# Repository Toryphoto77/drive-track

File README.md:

# 驰迹 DriveTrack

> 把每一次驾驶，记录成能被复盘的数据。

驰迹是一款为「认真开车的人」做的驾驶记录 App：汽车、摩托、卡丁车三种模式，一键开始记录。轨迹、车速、G 值、姿态、定位精度全程留存，赛道日还能自动计时、逐圈复盘。

黑色 HUD 界面，没有导航式的杂乱信息：开的时候只看该看的，停下来再慢慢看数据。

## 我们想做的事

市面上的行车记录大多停在「画一条线」这一步：轨迹有了，但看不出哪一脚刹车早了、哪一个弯出得慢了。驰迹想把它往前推一步——同一份数据，既能在赛道上告诉你这一圈差在哪，也能在日常通勤后告诉你这段路开得稳不稳。

三条原则贯穿整个产品：

- **记录不该打扰驾驶**：记录界面只有必要的数字，语音播报代替盯屏，倒计时带强震反馈。
- **数据留在你手里**：默认只存本机，云端上传、公开行程都是手动操作，不做自动同步。
- **结论要看得懂**：不给一串看不懂的曲线，给圈速、Delta、分段着色和一句能执行的提示。

## 核心功能

### 三种模式

- **汽车 / 摩托**：街道记录，超速与 GPS 丢失语音提醒，出行天气播报。
- **卡丁车**：为赛道日准备的精简计时界面——大号圈速、圈号、左右两道 Delta 色条，扫一眼就知道快慢。
- 历史里的骑行行程仍可正常打开与查看。

### 赛道计时

- 进入赛道或卡丁前会校验外接定位是否就绪（是否连接、是否只输出二进制、是否已有定位、采样率是否达到 5Hz），不满足时直接说明原因并跳到设备页，避免记出一堆无效数据。
- 过线瞬间三重反馈：语音播报圈速、短震动、全屏闪一帧（绿色代表个人最佳，红色代表慢于参照）。
- 大字当前圈 + 分段着色 + 官方分段点 + 带符号 Delta，默认以本场最佳圈为参照。
- 赛道库收录 F1、中国系列与经典赛道共 78 条，几何逐条核对，长度对照 FIA 官方数据。
- 0–100 / 100–0 性能测试；驾驶习惯评分，扣分项逐条透明可见。

### 赛后复盘

- 数据页为车队遥测风格：速度、海拔、弯道曲线共用一条时间轴联动。
- 完赛汇总：圈速折线配逐圈数据（最佳圈高亮），给出中位圈、平均圈、圈速标准差与一致性，一眼看出这场的节奏是稳还是崩。
- 曲线 + 着色线路，不依赖视频也能复盘。
- 行程可导出、可分享；赛道包支持官方更新与本地编辑，官方更新不会覆盖你的改动。

### 外接设备

- 单入口扫描外接定位：DEXIAN D1、RaceBox、Dragy、Qstarz 等，通用 NMEA 兼容（私有协议以实测为准）。
- 自研 GPS + IMU 硬件方案推进中（ESP32-S3 + NEO-M9N + BMI088 + 气压计，车顶安装）。

### 云端（可选）

- 不登录也能用完整体验；登录后行程只在你点上传时才上传。
- 行程与公开资料可设为公开，默认仅本人可见。

## 下载

最新版见 [Releases](https://github.com/Toryphoto77/drive-track/releases/latest)（当前 v1.7.4）。按手机架构选一个，大多数手机用 arm64-v8a：

| 安装包 | 适用机型 |
| --- | --- |
| `DriveTrack-v*-release-arm64-v8a.apk` | 绝大多数安卓手机 |
| `DriveTrack-v*-release-armeabi-v7a.apk` | 老款 32 位手机 |
| `DriveTrack-v*-release-x86_64.apk` | x86 平板 / 模拟器 |

直接覆盖安装即可升级，不要卸载重装（本机行程存在本地，卸载会丢）。

App 内「关于 → 检查更新」会自动匹配当前架构的安装包，并对下载文件做 SHA-256 校验。

## 已知限制

- 传感器零偏校准只存内存，重启 App 需重新校零。
- 外接定位协议以通用 NMEA 为主，私有协议设备以实测为准。
- 路网来自公开 Overpass 服务，服务繁忙或网络不通时会提示失败原因，可手动重拉，上次成功的数据按位置缓存。
- 个人页填写的邮箱只存本机，不用于登录。

## 反馈

问题、建议、赛道数据纠错都欢迎提 [Issue](https://github.com/Toryphoto77/drive-track/issues)。

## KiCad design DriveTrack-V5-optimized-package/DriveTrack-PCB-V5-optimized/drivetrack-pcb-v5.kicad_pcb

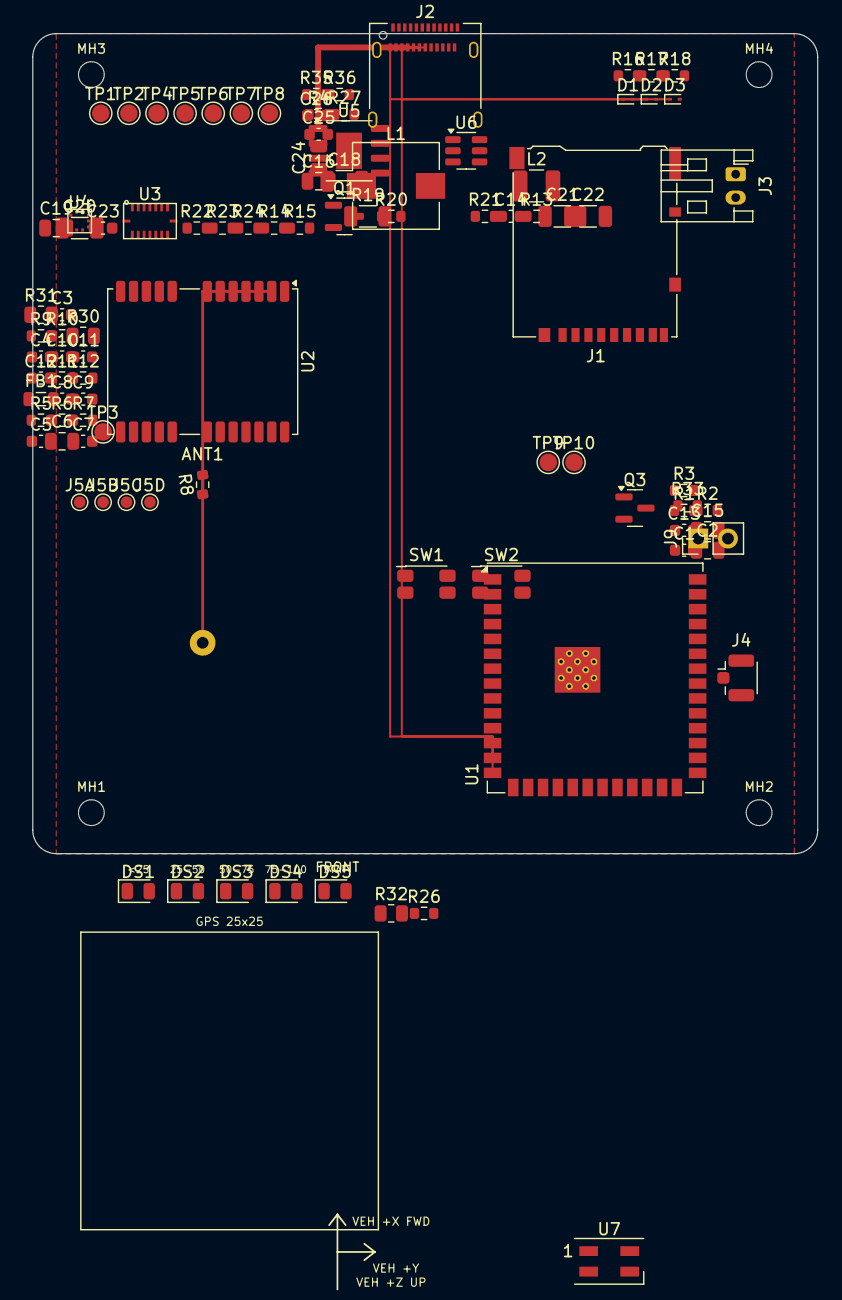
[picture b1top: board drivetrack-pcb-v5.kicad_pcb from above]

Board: 4 copper layers, 67.0 x 70.0 mm, 103 parts (0 on the bottom side), 63 nets.

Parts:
ANT1: GPS_Patch_25x25
C1, C4, C5, C7, C8, C9, C11, C12, C13, C14, C23, C25, C26: 100n; C_0603_1608Metric
C2, C6, C15, C16, C19, C24: 10u; C_0805_2012Metric
C3, C10: 1u; C_0603_1608Metric
C18, C20, C21, C22: 22u; C_1206_3216Metric
D1: ESD9B5.0ST5G; D_SOD-923
D2, D3: ESD9B3.3ST5G; D_SOD-923
DS1, DS2, DS3, DS4, DS5: LED 0805; LED_0805_2012Metric
FB1: FB 120R@100MHz; L_0805_2012Metric
J1: microSD push-push; microSD_HC_Hirose_DM3AT-SF-PEJM5
J2: USB-C 16P; USB_C_Receptacle_Amphenol_12401610E4-2A
J3: JST-PH 2.0mm; JST_PH_S2B-PH-K_1x02_P2.00mm_Horizontal
J4: U.FL (DNI); U.FL_Hirose_U.FL-R-SMT-1_Vertical
J5A: UART0_TX; TestPoint_Pad_D1.0mm
J5B: UART0_RX; TestPoint_Pad_D1.0mm
J5C: +3V3; TestPoint_Pad_D1.0mm
J5D: GND; TestPoint_Pad_D1.0mm
J9: solder pads DNI; PinHeader_1x02_P2.54mm_Vertical
L1: 1u; L_7.3x7.3_H4.5
L2: 2.2u; L_1210_3225Metric
MH1, MH2, MH3, MH4: MH 2.2mm NPTH; MountingHole_2.2mm
Q1, Q3: 2N7002; SOT-23
R1, R2, R5, R6, R9, R10, R13, R14, R15, R23: 10k; R_0603_1608Metric
R3: 330; R_0603_1608Metric
R4: 0.5R; R_0603_1608Metric
R7, R8, R18: 0R; R_0603_1608Metric
R11, R12: 4.7k; R_0603_1608Metric
R16, R17: 5.1k; R_0603_1608Metric
R19: 100R; R_1206_3216Metric
R20, R33: 1k; R_0603_1608Metric
R21, R24, R35, R36: 100k; R_0603_1608Metric
R22: 33k; R_0603_1608Metric
R26: 330R; R_0603_1608Metric
R27: 2R; R_0603_1608Metric
R30, R31: 100k; R_0805_2012Metric
R32: 330; R_0805_2012Metric
SW1: BOOT; SW_SPST_EVQP7A
SW2: RST; SW_SPST_EVQP7A
TP1: TP +3V3; TestPoint_Pad_D1.5mm
TP2: TP GND; TestPoint_Pad_D1.5mm
TP3: TP GPS_PPS; TestPoint_Pad_D1.5mm
TP4: TP BAT; TestPoint_Pad_D1.5mm
TP5: TP VBAT_DIV; TestPoint_Pad_D1.5mm
TP6: TP UART0_TX; TestPoint_Pad_D1.5mm
TP7: TP UART0_RX; TestPoint_Pad_D1.5mm
TP8: TP IO2; TestPoint_Pad_D1.5mm
TP9: TP KEY; TestPoint_Pad_D1.5mm
TP10: TP KEY_GND; TestPoint_Pad_D1.5mm
U1: ESP32-S3-WROOM-1U-N16R8; ESP32-S3-WROOM-1U
U2: NEO-M9N; ublox_NEO
U3: BMI088; BMI088_LGA-16_3.0x4.5mm
U4: BMP390; BMP390_LGA-10_2.0x2.0mm
U5: IP5306; IP5306_eSOP-8_3.9x4.9mm_EP2.21x3.10
U6: TPS563201; SOT-23-6
U7: SK6812MINI; LED_SK6812MINI_PLCC4_3.5x3.5mm_P1.75mm

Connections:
+3V3: C1.2, C2.2, C4.2, C9.2, C10.2, C11.2, C12.2, C13.2, C14.2, C15.2, C21.2, C22.2, FB1.2, J1.4, J5C.1, L2.2, R1.2, R2.2, R9.2, R10.2, R11.2, R12.2, R13.2, R14.2, R15.2, R22.1, TP1.1, U1.2, U3.3, U3.11, U4.1, U4.5, U4.6, U4.10, U7.4
+5V: C19.2, C20.1, C25.1, R19.1, R24.1, U5.8, U6.3
BARO_SCL: R12.1, U1.17, U4.2
BARO_SDA: R11.1, U1.12, U4.4
BAT: C18.2, J3.1, J9.1, L1.2, R4.1, R30.1, TP4.1
BOOT: R1.1, SW1.1, U1.27
DUMMY_EN: R20.2, U1.23
EN: C3.2, R2.1, SW2.1, U1.3
GND: C1.1, C2.1, C3.1, C4.1, C5.1, C6.1, C7.1, C8.1, C9.1, C10.1, C11.1, C12.1, C13.1, C14.1, C15.1, C16.1, C18.1, C19.1, C20.2, C21.1, C22.1, C24.1, C25.2, C26.2, D1.2, D2.2, D3.2, DS1.1, DS2.1, DS3.1, DS4.1, DS5.1, J1.6, J1.9, J1.11, J2.A1, J2.A12, J2.B1, J2.B12, J3.2, J4.2, J5D.1, J9.2, Q1.2, Q3.2, R16.1, R17.1, R18.2, R21.1, R23.1, R31.2, R36.2, SW1.2, SW2.2, TP2.1, TP10.1, U1.1, U1.40, U1.41, U2.7, U2.10, U2.12, U2.13, U2.24, U3.2, U3.4, U3.6, U3.7, U4.3, U4.8, U4.9, U5.9, U6.1, U7.2
GPS_PPS: TP3.1, U1.4, U2.3
GPS_RF: R8.2, U2.11
GPS_RX: U1.11, U2.20
GPS_TX: U1.10, U2.21
GPS_VCC: C5.2, C6.2, C7.2, FB1.1, R5.2, R6.2, R7.1, R7.2, U2.22, U2.23
IMU_CS1: R9.1, U1.18, U3.14
IMU_CS2: R10.1, U1.19, U3.5
IMU_INT1: U1.5, U3.16
IMU_INT3: U1.6, U3.12
IMU_MISO: U1.9, U3.10, U3.15
IMU_MOSI: U1.8, U3.9
IMU_SCK: U1.22, U3.8
IO2: R32.2, TP8.1, U1.38
KEY: Q3.3, TP9.1, U5.5
KEY_CTRL: R33.1, U1.34
KEY_GATE: Q3.1, R33.2
LED1: DS1.2, U5.2
LED2: DS2.2, U5.3
LED3: DS3.2, U5.4
LED4: DS4.2, R32.1
M9N_RESET: R6.1, U2.8
M9N_SAFEBOOT: R5.1, U2.1
unnamed: ANT1.1, R8.1
unnamed: C24.2, R27.1
unnamed: J2.S1, R18.1
unnamed: Q1.3, R19.2
unnamed: Q1.1, R20.1, R21.2
unnamed: C8.2, U2.9
unnamed: R4.2, U5.6
unnamed: L1.1, U5.7
unnamed: R24.2, U6.5
unnamed: C23.2, L2.1, U6.2
unnamed: C23.1, U6.6
unnamed: R22.2, R23.2, U6.4
unnamed: R3.1, U7.3
RGB_DIN: R3.2, U1.25
SD_CD: J1.10, R15.1, U1.21
SD_CS: J1.2, U1.20
SD_DAT1: J1.8, R13.1
SD_DAT2: J1.1, R14.1
SD_MISO: J1.7, U1.33
SD_MOSI: J1.3, U1.32
SD_SCK: J1.5, U1.31
STAT_ANODE: DS5.2, R26.1
STAT_LED: R26.2, U1.7
UART0_RX: J5B.1, TP7.1, U1.36
UART0_TX: J5A.1, TP6.1, U1.37
USB_CC1: J2.A5, R16.2
USB_CC2: J2.B5, R17.2
USB_DM: D3.1, J2.A7, J2.B7, U1.13
USB_DP: D2.1, J2.A6, J2.B6, U1.14
VBAT_DIV: R30.2, R31.1, TP5.1, U1.39
VBUS: C16.2, D1.1, J2.A4, J2.A9, J2.B4, J2.B9, R27.2, R35.1, U5.1
VBUS_DET: C26.1, R35.2, R36.1, U1.35

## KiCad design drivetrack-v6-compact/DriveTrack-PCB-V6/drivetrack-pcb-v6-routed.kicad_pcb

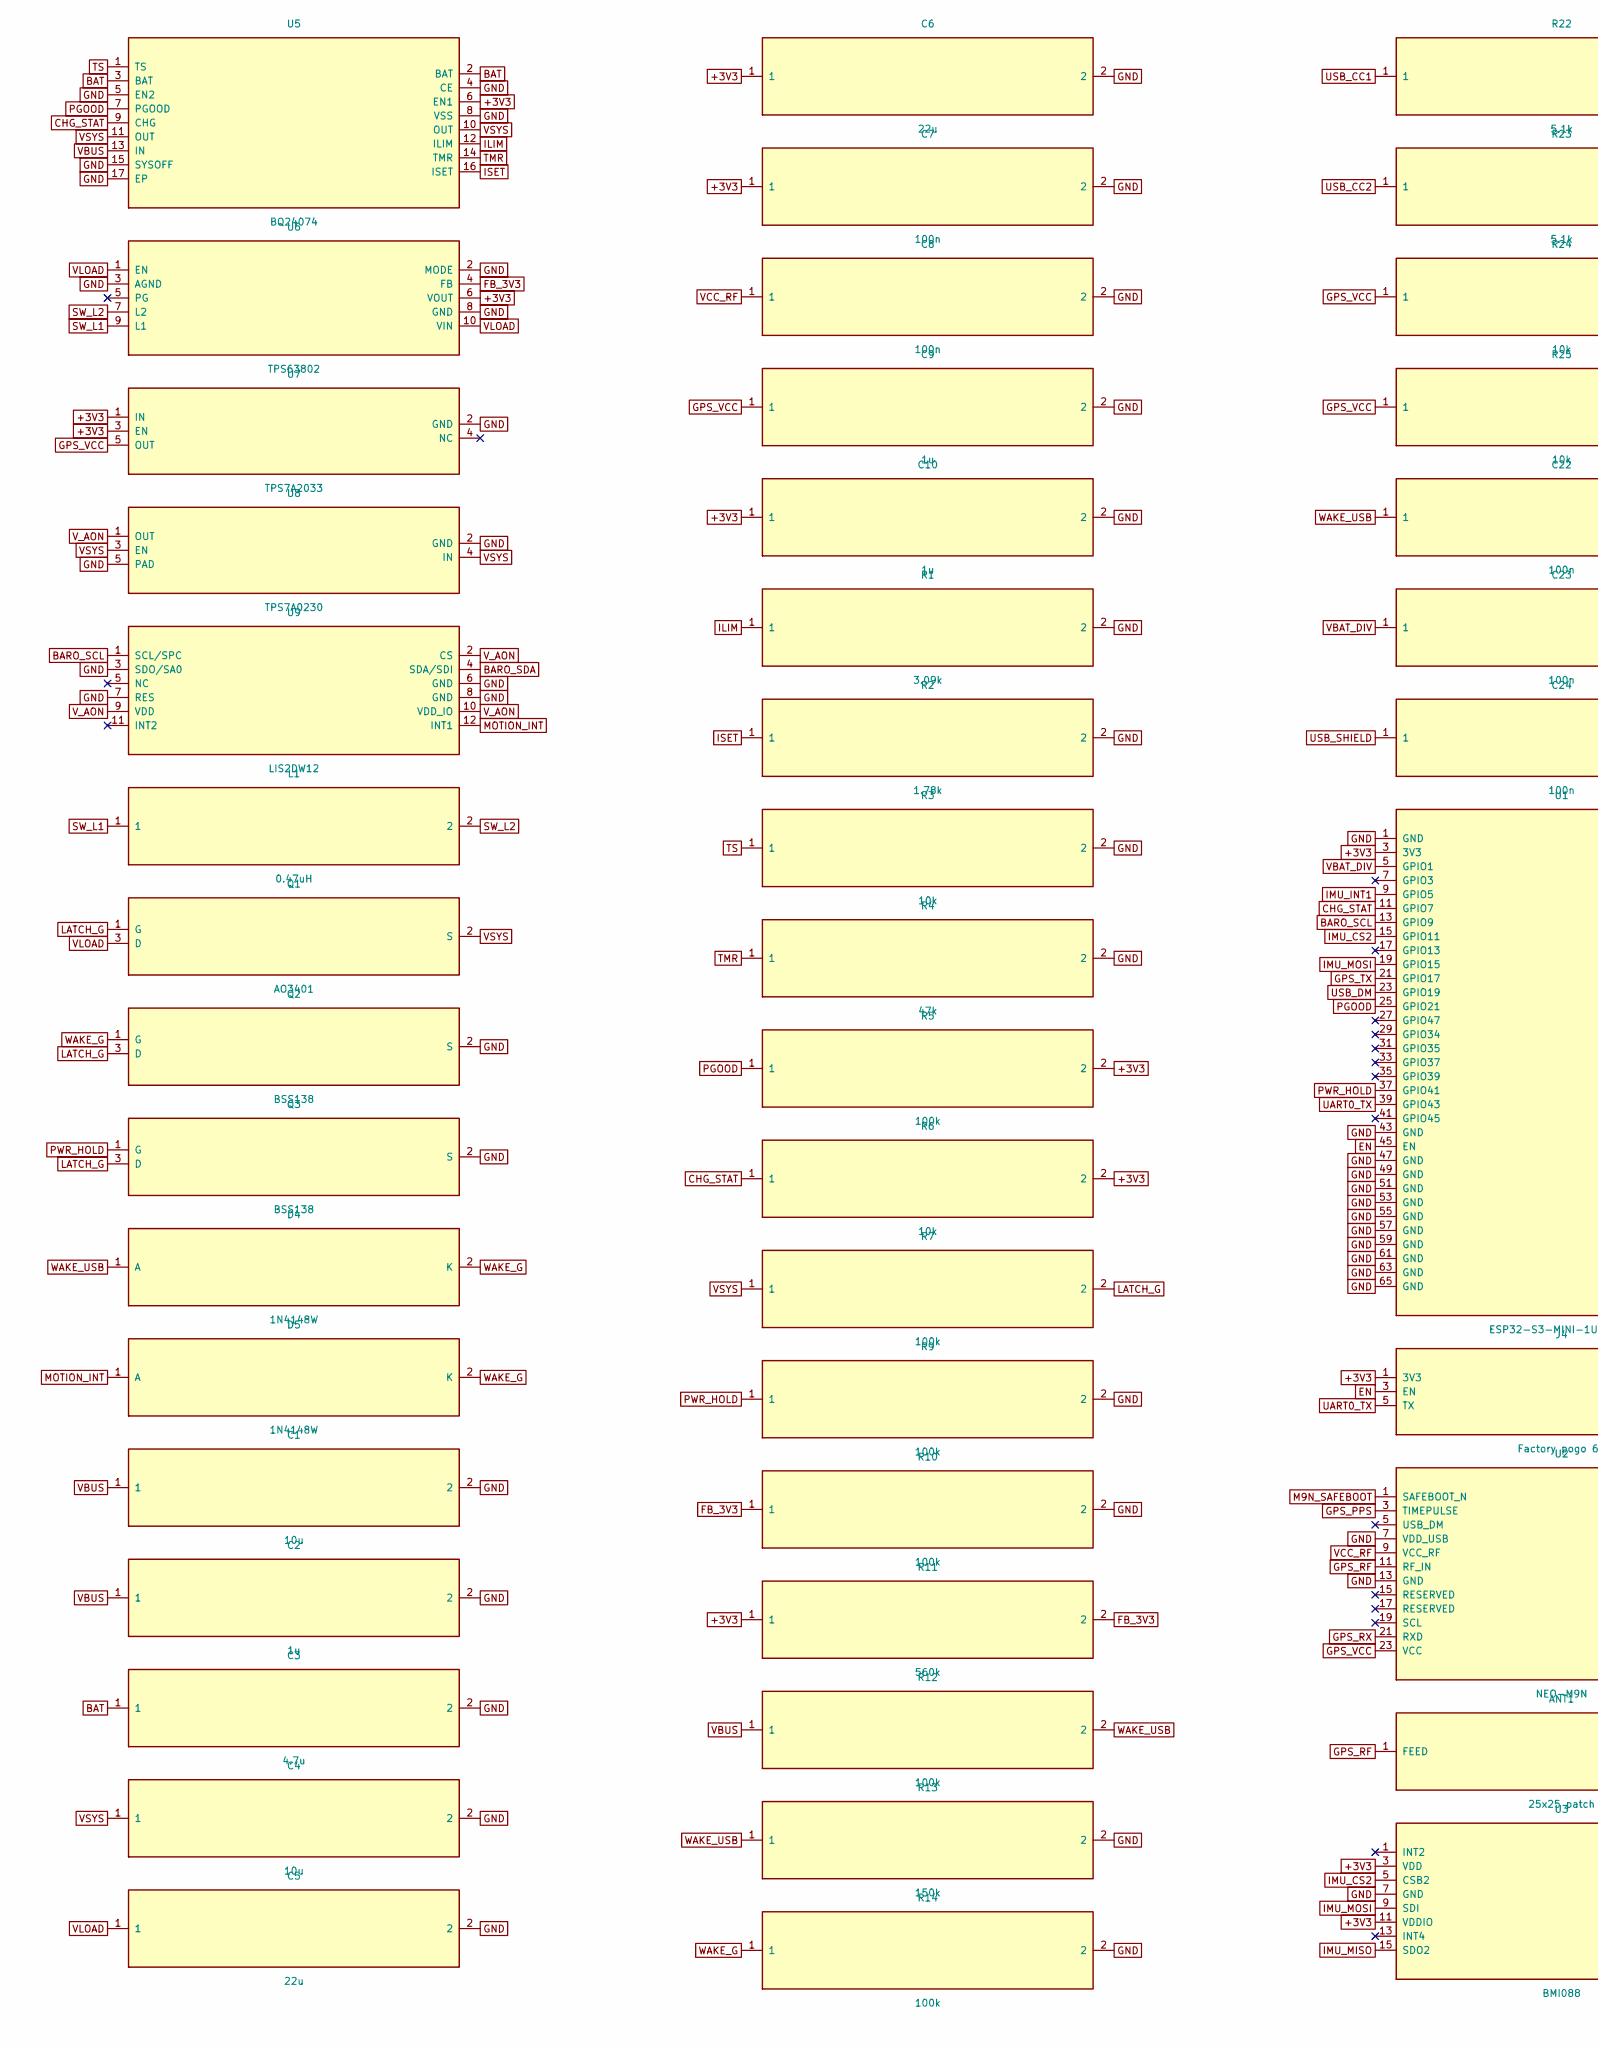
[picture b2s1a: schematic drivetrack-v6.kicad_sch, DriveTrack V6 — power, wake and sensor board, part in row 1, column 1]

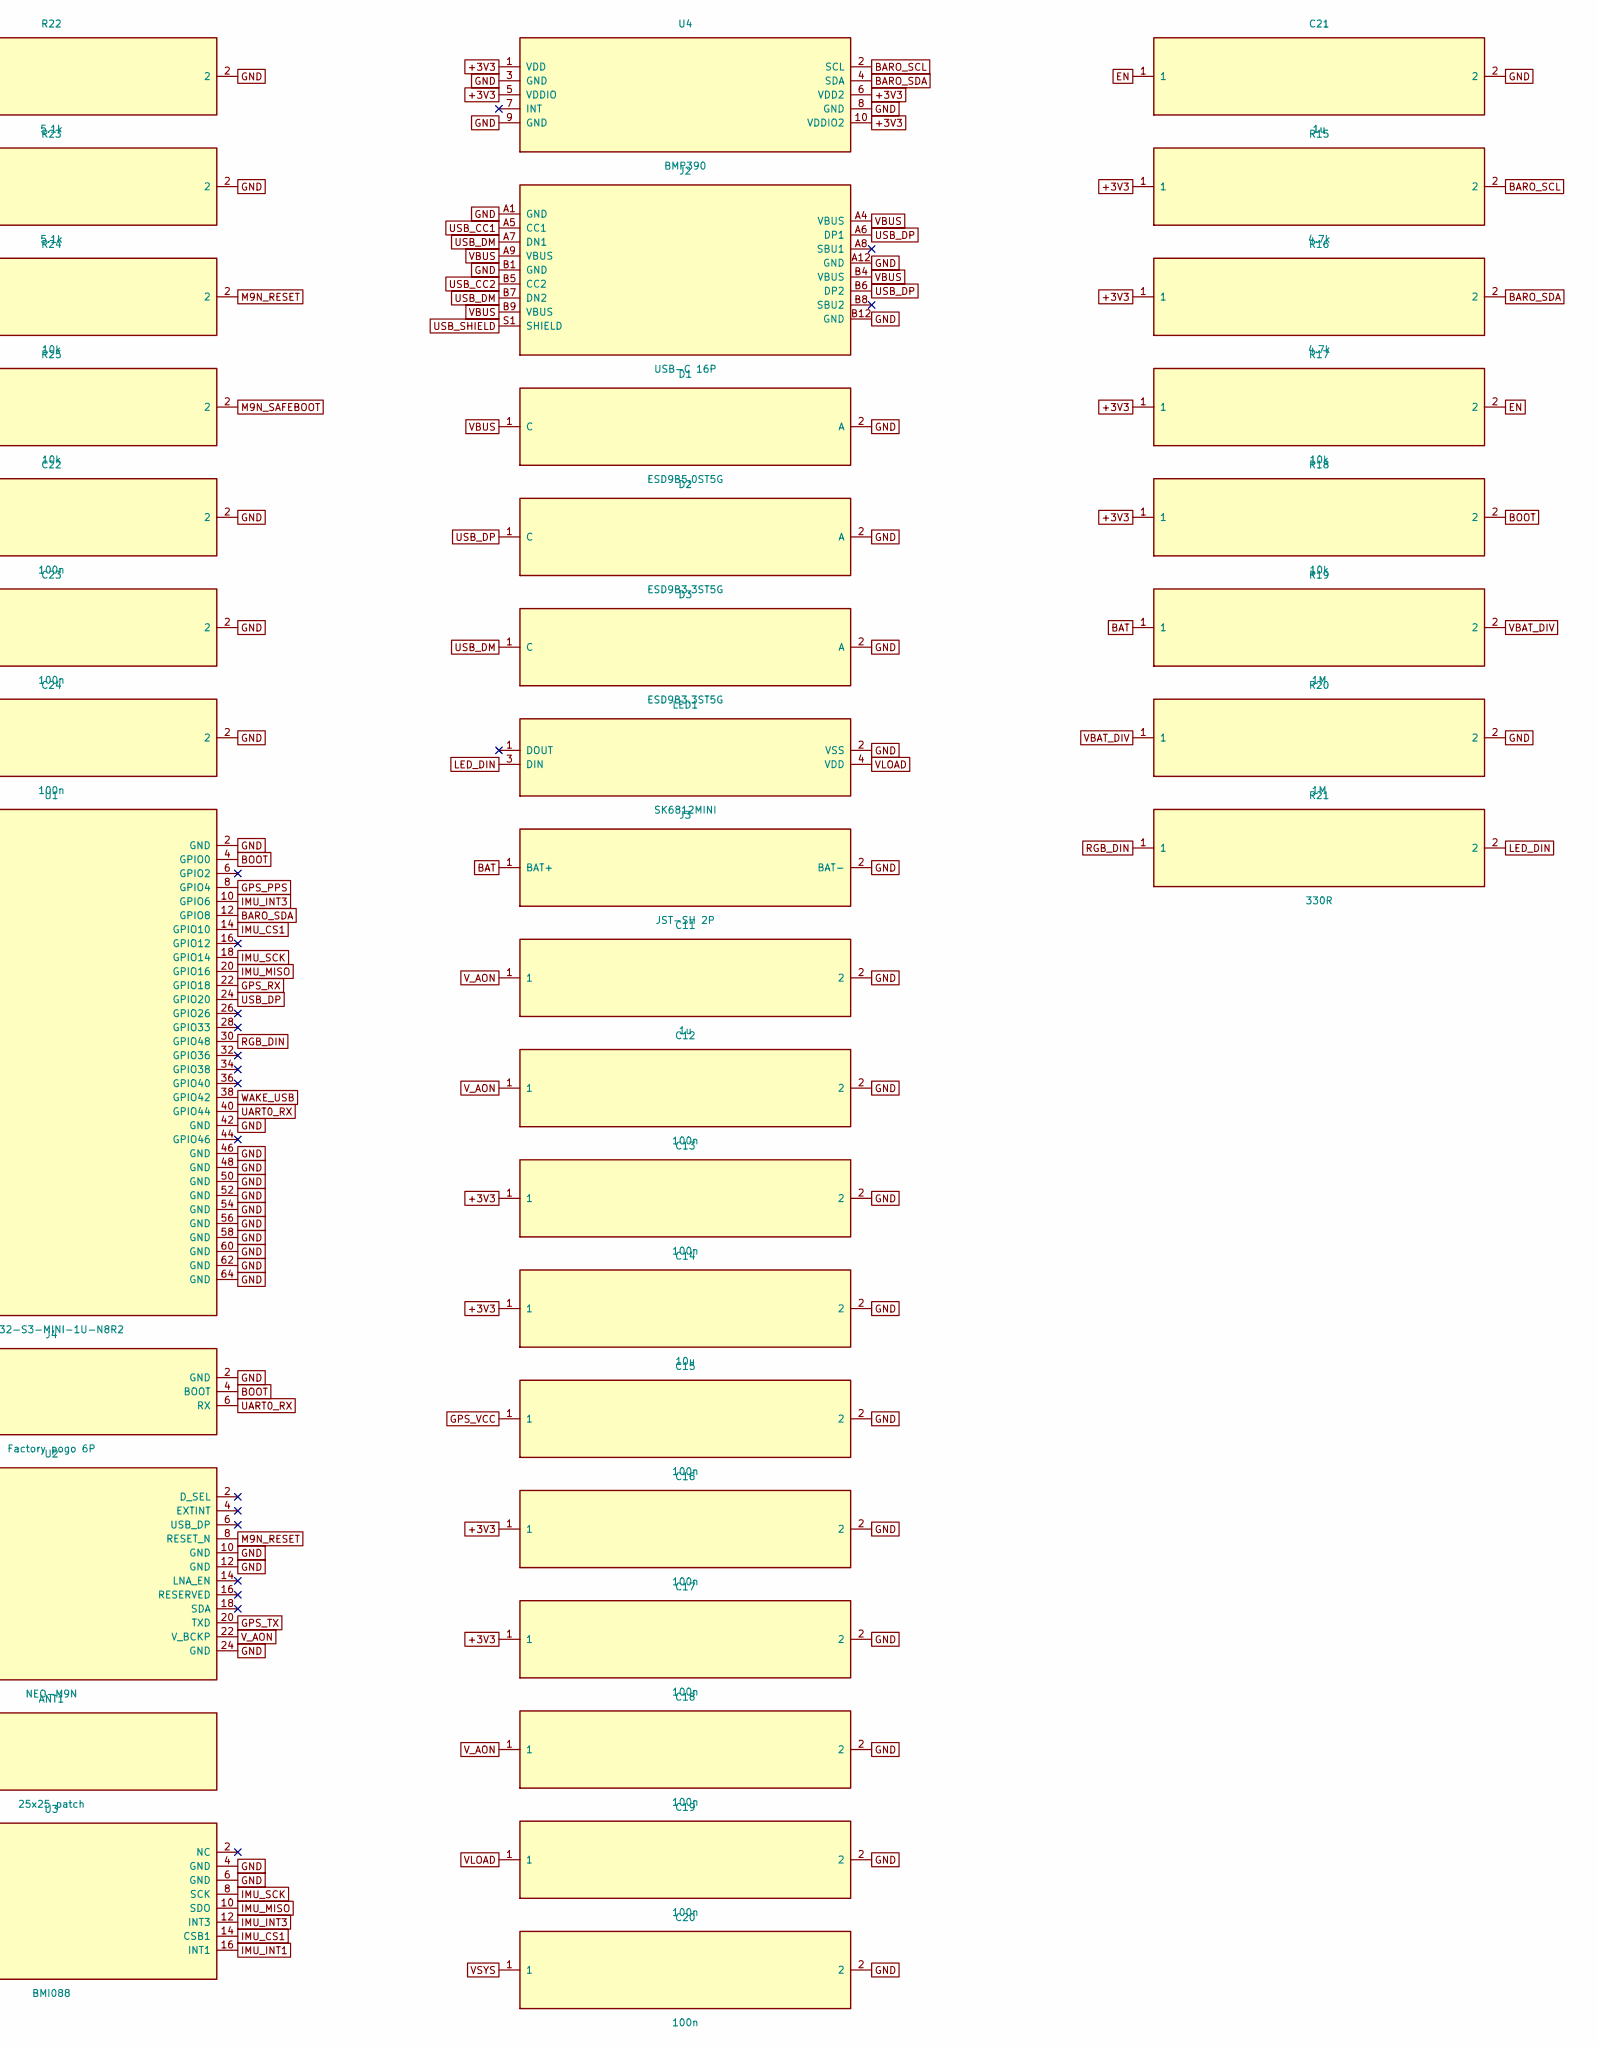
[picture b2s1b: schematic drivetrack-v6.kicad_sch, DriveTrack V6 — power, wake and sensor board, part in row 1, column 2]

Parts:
ANT1: 25x25 patch; GPS_Patch_25x25
C1, C4, C14: 10u; C_0805_2012Metric
C2, C9, C10, C11, C21: 1u; C_0603_1608Metric
C3: 4.7u; C_0805_2012Metric
C5, C6: 22u; C_0805_2012Metric
C7, C8, C12, C13, C15, C16, C17, C18, C19, C20, C22, C23, C24: 100n; C_0402_1005Metric
D1: ESD9B5.0ST5G; D_SOD-923
D2, D3: ESD9B3.3ST5G; D_SOD-923
D4, D5: 1N4148W; D_SOD-323
J2: USB-C 16P; USB_C_Receptacle_Amphenol_12401610E4-2A
J3: JST-SH 2P; JST_SH_SM02B-SRSS-TB_1x02-1MP_P1.00mm_Horizontal
J4: Factory pogo 6P; Pogo_6_1.5mm
L1: 0.47uH; L_4x4_H2
LED1: SK6812MINI; LED_SK6812MINI_PLCC4_3.5x3.5mm_P1.75mm
Q1: AO3401; SOT-23
Q2, Q3: BSS138; SOT-23
R1: 3.09k; R_0402_1005Metric
R2: 1.78k; R_0402_1005Metric
R3, R6, R17, R18, R24, R25: 10k; R_0402_1005Metric
R4: 47k; R_0402_1005Metric
R5, R7, R9, R10, R12, R14: 100k; R_0402_1005Metric
R11: 560k; R_0402_1005Metric
R13: 150k; R_0402_1005Metric
R15, R16: 4.7k; R_0402_1005Metric
R19, R20: 1M; R_0402_1005Metric
R21: 330R; R_0402_1005Metric
R22, R23: 5.1k; R_0402_1005Metric
U1: ESP32-S3-MINI-1U-N8R2; ESP32-S3-MINI-1
U2: NEO-M9N; ublox_NEO
U3: BMI088; BMI088_LGA-16_3.0x4.5mm
U4: BMP390; BMP390_LGA-10_2.0x2.0mm
U5: BQ24074; VQFN-16-1EP_3x3mm_P0.5mm_EP1.6x1.6mm
U6: TPS63802; VSON-10-3x2mm_P0.5mm_TPS63802
U7: TPS7A2033; SOT-23-5
U8: TPS7A0230; Texas_X2SON-4_1x1mm_P0.65mm
U9: LIS2DW12; LGA-12_2x2mm_P0.5mm

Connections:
+3V3: C6.1, C7.1, C10.1, C13.1, C14.1, C16.1, C17.1, J4.1 (3V3), R5.2, R6.2, R11.1, R15.1, R16.1, R17.1, R18.1, U1.3 (3V3), U3.3 (VDD), U3.11 (VDDIO), U4.1 (VDD), U4.5 (VDDIO), U4.6 (VDD2), U4.10 (VDDIO2), U5.6 (EN1), U6.6 (VOUT), U7.1 (IN), U7.3 (EN)
BARO_SCL: R15.2, U1.13 (GPIO9), U4.2 (SCL), U9.1 (SCL/SPC)
BARO_SDA: R16.2, U1.12 (GPIO8), U4.4 (SDA), U9.4 (SDA/SDI)
BAT: C3.1, J3.1 (BAT+), R19.1, U5.2 (BAT), U5.3 (BAT)
BOOT: J4.4 (BOOT), R18.2, U1.4 (GPIO0)
CHG_STAT: R6.1, U1.11 (GPIO7), U5.9 (CHG)
EN: C21.1, J4.3 (EN), R17.2, U1.45 (EN)
FB_3V3: R10.1, R11.2, U6.4 (FB)
GND: C1.2, C2.2, C3.2, C4.2, C5.2, C6.2, C7.2, C8.2, C9.2, C10.2, C11.2, C12.2, C13.2, C14.2, C15.2, C16.2, C17.2, C18.2, C19.2, C20.2, C21.2, C22.2, C23.2, C24.2, D1.2 (A), D2.2 (A), D3.2 (A), J2.A1 (GND), J2.A12 (GND), J2.B1 (GND), J2.B12 (GND), J3.2 (BAT-), J4.2 (GND), LED1.2 (VSS), Q2.2 (S), Q3.2 (S), R1.2, R2.2, R3.2, R4.2, R9.2, R10.2, R13.2, R14.2, R20.2, R22.2, R23.2, U1.1 (GND), U1.2 (GND), U1.42 (GND), U1.43 (GND), U1.46 (GND), U1.47 (GND), U1.48 (GND), U1.49 (GND), U1.50 (GND), U1.51 (GND), U1.52 (GND), U1.53 (GND), U1.54 (GND), U1.55 (GND), U1.56 (GND), U1.57 (GND), U1.58 (GND), U1.59 (GND), U1.60 (GND), U1.61 (GND), U1.62 (GND), U1.63 (GND), U1.64 (GND), U1.65 (GND), U2.7 (VDD_USB), U2.10 (GND), U2.12 (GND), U2.13 (GND), U2.24 (GND), U3.4 (GND), U3.6 (GND), U3.7 (GND), U4.3 (GND), U4.8 (GND), U4.9 (GND), U5.4 (CE), U5.5 (EN2), U5.8 (VSS), U5.15 (SYSOFF), U5.17 (EP), U6.2 (MODE), U6.3 (AGND), U6.8 (GND), U7.2 (GND), U8.2 (GND), U8.5 (PAD), U9.3 (SDO/SA0), U9.6 (GND), U9.7 (RES), U9.8 (GND)
GPS_PPS: U1.8 (GPIO4), U2.3 (TIMEPULSE)
GPS_RF: ANT1.1, U2.11 (RF_IN)
GPS_RX: U1.22 (GPIO18), U2.21 (RXD)
GPS_TX: U1.21 (GPIO17), U2.20 (TXD)
GPS_VCC: C9.1, C15.1, R24.1, R25.1, U2.23 (VCC), U7.5 (OUT)
ILIM: R1.1, U5.12 (ILIM)
IMU_CS1: U1.14 (GPIO10), U3.14 (CSB1)
IMU_CS2: U1.15 (GPIO11), U3.5 (CSB2)
IMU_INT1: U1.9 (GPIO5), U3.16 (INT1)
IMU_INT3: U1.10 (GPIO6), U3.12 (INT3)
IMU_MISO: U1.20 (GPIO16), U3.10 (SDO), U3.15 (SDO2)
IMU_MOSI: U1.19 (GPIO15), U3.9 (SDI)
IMU_SCK: U1.18 (GPIO14), U3.8 (SCK)
ISET: R2.1, U5.16 (ISET)
LATCH_G: Q1.1 (G), Q2.3 (D), Q3.3 (D), R7.2
LED_DIN: LED1.3 (DIN), R21.2
M9N_RESET: R24.2, U2.8 (RESET_N)
M9N_SAFEBOOT: R25.2, U2.1 (SAFEBOOT_N)
MOTION_INT: D5.1 (A), U9.12 (INT1)
PGOOD: R5.1, U1.25 (GPIO21), U5.7 (PGOOD)
PWR_HOLD: Q3.1 (G), R9.1, U1.37 (GPIO41)
RGB_DIN: R21.1, U1.30 (GPIO48)
SW_L1: L1.1, U6.9 (L1)
SW_L2: L1.2, U6.7 (L2)
TMR: R4.1, U5.14 (TMR)
TS: R3.1, U5.1 (TS)
UART0_RX: J4.6 (RX), U1.40 (GPIO44)
UART0_TX: J4.5 (TX), U1.39 (GPIO43)
USB_CC1: J2.A5 (CC1), R22.1
USB_CC2: J2.B5 (CC2), R23.1
USB_DM: D3.1 (C), J2.A7 (DN1), J2.B7 (DN2), U1.23 (GPIO19)
USB_DP: D2.1 (C), J2.A6 (DP1), J2.B6 (DP2), U1.24 (GPIO20)
USB_SHIELD: C24.1, J2.S1 (SHIELD)
VBAT_DIV: C23.1, R19.2, R20.1, U1.5 (GPIO1)
VBUS: C1.1, C2.1, D1.1 (C), J2.A4 (VBUS), J2.A9 (VBUS), J2.B4 (VBUS), J2.B9 (VBUS), R12.1, U5.13 (IN)
VCC_RF: C8.1, U2.9 (VCC_RF)
VLOAD: C5.1, C19.1, LED1.4 (VDD), Q1.3 (D), U6.1 (EN), U6.10 (VIN)
VSYS: C4.1, C20.1, Q1.2 (S), R7.1, U5.10 (OUT), U5.11 (OUT), U8.3 (EN), U8.4 (IN)
V_AON: C11.1, C12.1, C18.1, U2.22 (V_BCKP), U8.1 (OUT), U9.2 (CS), U9.9 (VDD), U9.10 (VDD_IO)
WAKE_G: D4.2 (K), D5.2 (K), Q2.1 (G), R14.1
WAKE_USB: C22.1, D4.1 (A), R12.2, R13.1, U1.38 (GPIO42)

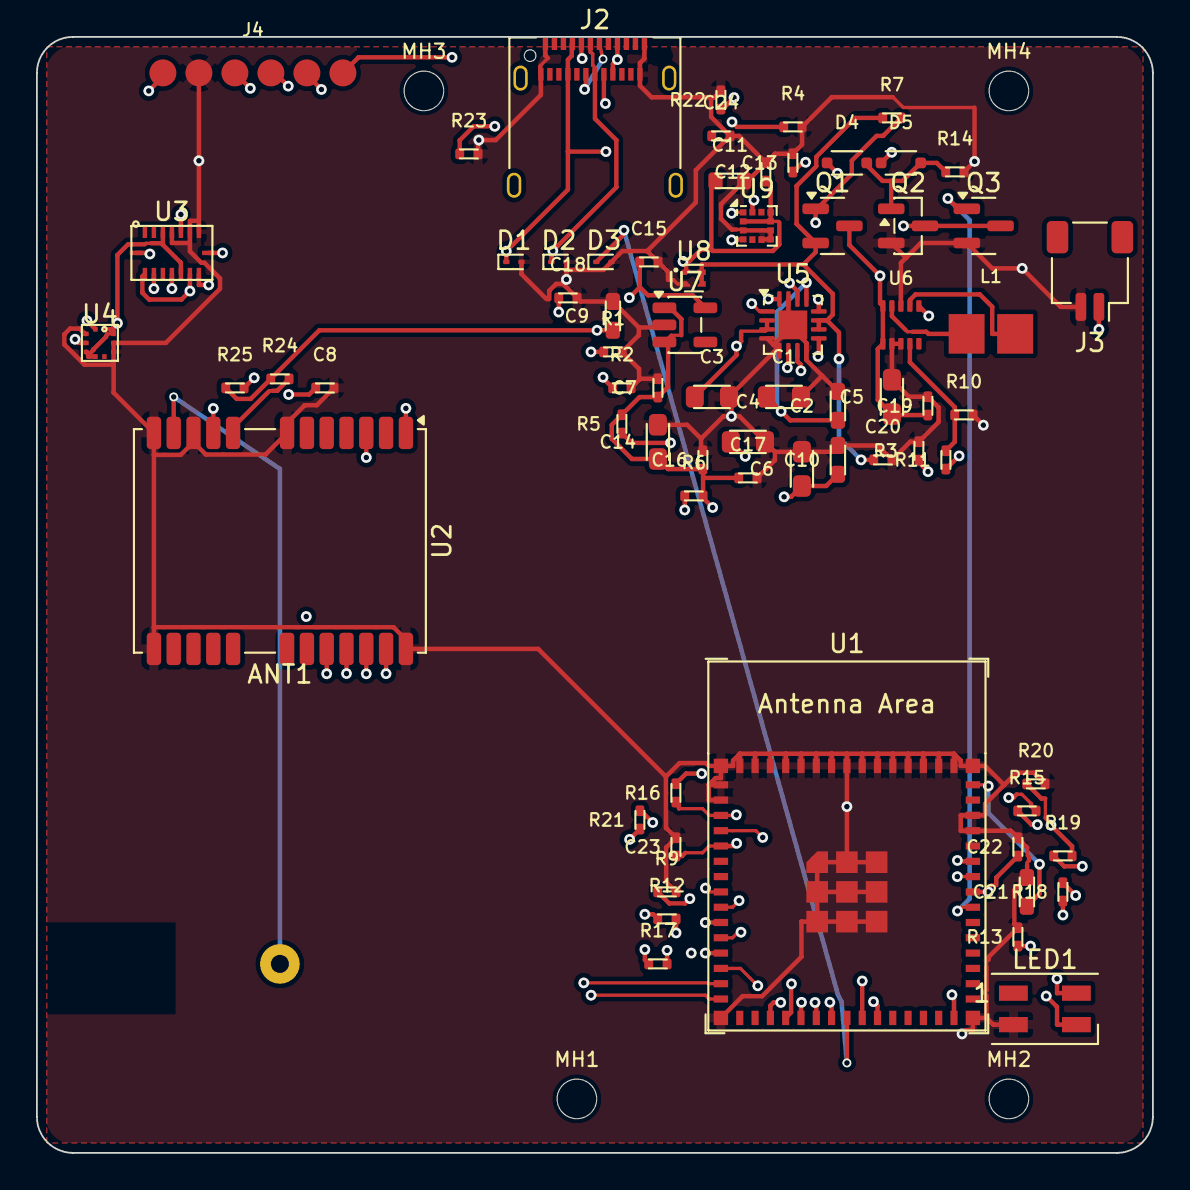
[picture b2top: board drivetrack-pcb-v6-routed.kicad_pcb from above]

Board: 4 copper layers, 62.0 x 62.0 mm, 75 parts (0 on the bottom side), 49 nets.

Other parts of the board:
MH1, MH2, MH3, MH4: M2 NPTH; MountingHole_2.2mm

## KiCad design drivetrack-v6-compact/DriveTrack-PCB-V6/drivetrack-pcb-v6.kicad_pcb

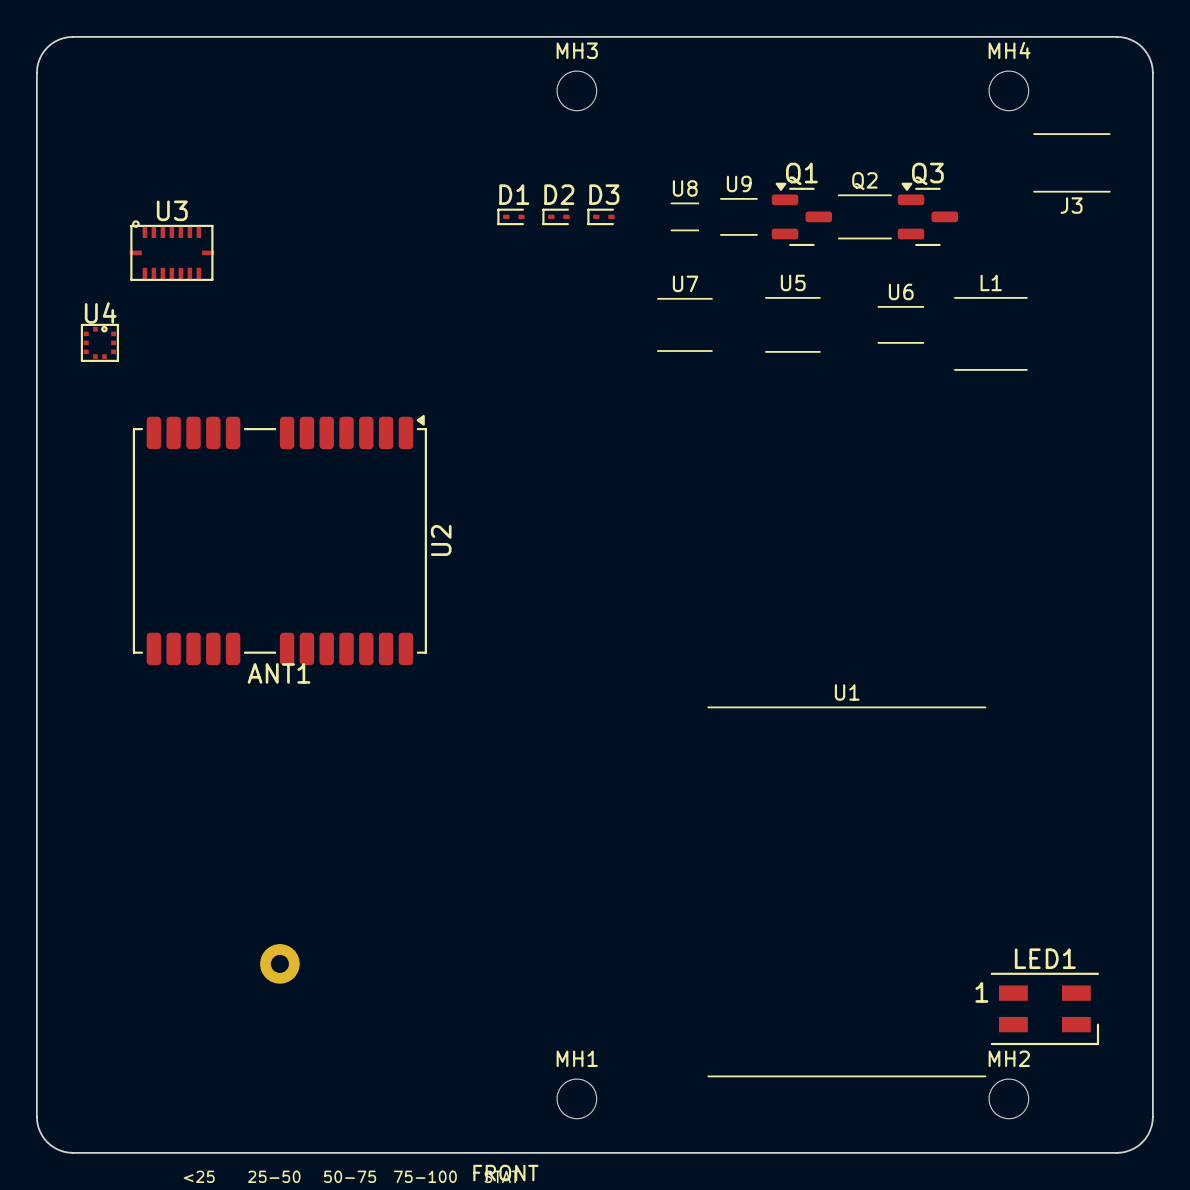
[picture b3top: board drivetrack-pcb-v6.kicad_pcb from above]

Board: 4 copper layers, 62.0 x 62.0 mm, 23 parts (0 on the bottom side), 4 nets, no tracks yet.

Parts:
ANT1: GPS_Patch_25x25
D1: ESD9B5.0ST5G; D_SOD-923
D2, D3: ESD9B3.3ST5G; D_SOD-923
J3: JST-SH 1.0mm 2P; PLACEHOLDER_J3
L1: 1uH 4x4x2; PLACEHOLDER_L1
LED1: SK6812MINI RGB; LED_SK6812MINI_PLCC4_3.5x3.5mm_P1.75mm
MH1, MH2, MH3, MH4: MH 2.2mm NPTH; MountingHole_2.2mm
Q1: AO3401; SOT-23
Q2: 2N7002; PLACEHOLDER_Q2
Q3: 2N7002; SOT-23
U1: ESP32-S3-MINI-1U-N8R2; PLACEHOLDER_U1
U2: NEO-M9N; ublox_NEO
U3: BMI088; BMI088_LGA-16_3.0x4.5mm
U4: BMP390; BMP390_LGA-10_2.0x2.0mm
U5: BQ24074; PLACEHOLDER_U5
U6: TPS63802; PLACEHOLDER_U6
U7: TPS7A2033; PLACEHOLDER_U7
U8: TPS7A0230; PLACEHOLDER_U8
U9: LIS2DW12; PLACEHOLDER_U9

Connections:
+3V3: LED1.4, U3.3, U3.11, U4.1, U4.5, U4.6, U4.10
GND: D1.2, D2.2, D3.2, LED1.2, Q1.2, Q3.2, U2.7, U2.10, U2.12, U2.13, U2.24, U3.2, U3.4, U3.6, U3.7, U4.3, U4.8, U4.9
GPS_VCC: U2.22, U2.23
IMU_MISO: U3.10, U3.15

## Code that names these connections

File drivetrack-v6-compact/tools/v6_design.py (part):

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# ---------------------------------------------------------------- MCU / RF
_esp = []
_esp += [("1", "GND", GND), ("2", "GND", GND), ("3", "3V3", V33)]
_esp += [("4", "GPIO0", "BOOT"), ("5", "GPIO1", "VBAT_DIV"),
         ("6", "GPIO2", ""), ("7", "GPIO3", ""), ("8", "GPIO4", "GPS_PPS"),
         ("9", "GPIO5", "IMU_INT1"), ("10", "GPIO6", "IMU_INT3"),
         ("11", "GPIO7", "CHG_STAT"), ("12", "GPIO8", "BARO_SDA"),
         ("13", "GPIO9", "BARO_SCL"), ("14", "GPIO10", "IMU_CS1"),
         ("15", "GPIO11", "IMU_CS2"), ("16", "GPIO12", ""),
         ("17", "GPIO13", ""), ("18", "GPIO14", "IMU_SCK"),
         ("19", "GPIO15", "IMU_MOSI"), ("20", "GPIO16", "IMU_MISO"),
         ("21", "GPIO17", "GPS_TX"), ("22", "GPIO18", "GPS_RX"),
         ("23", "GPIO19", "USB_DM"), ("24", "GPIO20", "USB_DP"),
         ("25", "GPIO21", "PGOOD"), ("26", "GPIO26", ""),
         ("27", "GPIO47", ""), ("28", "GPIO33", ""), ("29", "GPIO34", ""),
         ("30", "GPIO48", "RGB_DIN"), ("31", "GPIO35", ""), ("32", "GPIO36", ""),
         ("33", "GPIO37", ""), ("34", "GPIO38", ""), ("35", "GPIO39", ""),
         ("36", "GPIO40", ""), ("37", "GPIO41", "PWR_HOLD"), ("38", "GPIO42", "WAKE_USB"),
         ("39", "GPIO43", "UART0_TX"), ("40", "GPIO44", "UART0_RX"),
         ("41", "GPIO45", ""), ("42", "GND", GND), ("43", "GND", GND),
         ("44", "GPIO46", ""), ("45", "EN", "EN")]
_esp += [(str(n), "GND", GND) for n in range(46, 66)]
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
